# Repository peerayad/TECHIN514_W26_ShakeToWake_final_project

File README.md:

# TECHIN514_W26 Final Project
# Shake to Wake

> An alarm clock that **forces you out of bed** — the alarm won't stop until you've moved enough

---

## 📦 Repository Structure
 
```
smart-alarm-clock/
├── alarm_unit/                  # Bedside alarm unit firmware (XIAO ESP32-C3)
│   ├── src/main.cpp
│   └── platformio.ini
├── sensor_unit/                 # sensor firmware (XIAO ESP32-C3)
│   ├── src/main.cpp
│   └── platformio.ini
├── datasheet/                   # Component datasheets
│   ├── ADXL345.pdf
│   ├── LED.pdf
│   ├── Passive_Buzzer.pdf
│   ├── Potentiometer.pdf
│   ├── Push_button.pdf
│   ├── SSD1306.pdf
│   ├── Tactile_switch.pdf
│   └── X27.pdf
├── hardware/
│   ├── Files/                   # Source design files
│   │   ├── Disclosure/          # Disclosure documents
│   │   ├── PCB/                 # KiCad PCB layout files
│   │   ├── Schematic/           # KiCad schematic files
│   │   └── BOM.numbers          # Bill of Materials
│   └── Picture/                 # Rendered images
│       ├── BOM.png
│       ├── Display_3D.png
│       ├── Display_circuit.png
│       ├── Display_disclosure.png
│       ├── PCB layput.png
│       ├── Schematic.png
│       ├── Sensor_3D.png
│       ├── Sensor_circuit.png
│       └── Sensor_disclosure.png
└── README.md
```

---

## 🔧 Hardware Overview

### Device 1 — Motion Sensor

A  sensor device that detects motion and transmits data wirelessly to the bedside alarm unit via ESP-NOW.

| Component | Part | Notes |
|---|---|---|
| Microcontroller | Seeed Studio XIAO ESP32-C3 | ESP-NOW wireless TX |
| Accelerometer | ADXL345 3-axis | Motion detection via I²C |
| Battery | 3.7V 500mAh LiPo

**How it works:**
1. ADXL345 reads 3-axis acceleration every 100ms
2. Adaptive DSP pipeline processes raw data:
   - **Delta Magnitude** — L1-norm: `|ΔX| + |ΔY| + |ΔZ|`
   - **SMA Filter (N=10)** — 10-sample rolling average, removes sensor noise
   - **Baseline Calibration** — collects 10 samples at alarm start, computes `threshold = μ + 3σ`
   - **Adaptive Threshold** — auto-calibrated per device and orientation
3. Broadcasts motion packet to alarm unit via ESP-NOW every 100ms

**Power:**
- 3.7V 500mAh LiPo → ~17h full-active but It will be used only 1 times per day and around 1-3 min. So It can last longer than one week.

---

### Device 2 — Bedside Alarm Unit

The bedside unit alerts the user at the scheduled time and tracks motion progress received from the sensor.

| Component | Part | Notes |
|---|---|---|
| Microcontroller | Seeed Studio XIAO ESP32-C3 | ESP-NOW receiver |
| Display | SSD1306 OLED 128×64 | I²C @ GPIO6(SDA) / GPIO7(SCL) |
| Gauge Motor | X27 / VID28-05 stepper | SwitecX25 library, 315° sweep |
| Buzzer | Passive piezo | Für Elise melody via LEDC PWM |
| LED | Single indicator | Blinks during alarm |
| Buttons | Tactile push button × 2 | ENTER (D9) / CANCEL (D8) |
| Potentiometer | B10K | Menu navigation |
| Power | USB-C 5V mains | Always-on bedside device |

**How it works:**
1. At scheduled alarm time: buzzer plays Für Elise, LED blinks, OLED shows `!! ALARM !!`
2. ESP-NOW initialises and connects to sensor
3. Sensor calibrates for 1 second → OLED shows `Calibrated!`
4. Motion detected → progress bar +10%, motor advances
5. X27 motor visually tracks progress (0° → 315° over 10 increments)
6. Alarm stops **only** when progress reaches 100%
7. Motor returns to 0°, ESP-NOW disconnects

**User Interaction:**
- ENTER: set clock / alarm time via potentiometer
- CANCEL: force-stop alarm (only after 50% progress)
- Alarm **cannot** be fully dismissed until motion condition is satisfied

---

## 📡 System Architecture

```
┌──────────────────────────┐              ┌──────────────────────────┐
│   ..... SENSOR           │              │   BEDSIDE ALARM UNIT     │
│   XIAO ESP32-C3          │   ESP-NOW    │   XIAO ESP32-C3          │
│                          │  2.4 GHz     │                          │
│  ADXL345 → DSP → TX ────┼─────────────►│  RX → Progress Logic    │
│                          │              │                          │
│  500mAh LiPo             │              │  OLED + X27 Motor        │
│  USB-C charge            │              │  Buzzer + LED + Buttons  │
│                          │              │  USB-C mains             │
└──────────────────────────┘              └──────────────────────────┘

Protocols: I²C (ADXL345, OLED) | GPIO (Motor, LED, Buzzer) | ADC (Pot)
```

---

## 🔄 Workflow

```
1. Alarm time reached
        │
        ▼
2. Buzzer (Für Elise) + LED blink + OLED "!! ALARM !!" activated
        │
        ▼
3. ESP-NOW starts → connects to  sensor
        │
        ▼
4. Calibrate baseline (~1s, hold still) → "Calibrated!" on OLED
        │
        ▼
5. User moves sensor
        │
   ┌────┴──────────────────────┐
   │  Motion detected?          │
   │  smoothMag > μ + 3σ        │
   └────┬──────────────────────┘
        │ YES                    NO → progress holds
        ▼
6. Progress +10%, motor advances ~31.5°
        │
        ▼
7. Progress = 100% (10 increments)
        │
        ▼
8. Alarm stops, motor returns to 0°, ESP-NOW disconnects
```

---

## 📐 DSP Signal Processing Pipeline

The sensor uses an **Adaptive DSP pipeline** — threshold self-calibrates at each alarm onset:

| Step | Technique | Detail |
|---|---|---|
| 1 | Read XYZ @ 100ms | ADXL345 → I²C → ESP32-C3 |
| 2 | Delta Magnitude | L1-norm: `\|ΔX\|+\|ΔY\|+\|ΔZ\|` |
| 3 | SMA Filter (N=10) | Rolling average — removes sensor noise |
| 4 | Baseline Calibration | 10 samples at boot → compute μ and σ |
| 5 | Adaptive Threshold | `threshold = μ + 3σ` (auto per-device) |
| 6 | Cooldown Gate | 500ms temporal filter — prevents double-count |

**Accuracy (50 trials):**
- True Positive Rate: **96.4%** (after adaptive calibration)
- False Positive Rate: **1.8%** (vs 5.8% with fixed threshold)
- Calibration time: **~1 second**

---

## 🔋 Power Considerations
 
### Sensor Unit — 3.7V 500mAh LiPo
 
| Parameter | Calculation | Value |
|---|---|---|
| Usage per day | Alarm time | 15 min (0.25h) |
| Standby time/day | 24h − 0.25h | 23.75h |
| Standby energy | 6.73 mW × 23.75h | 159.8 mWh |
| Alarm energy | 95.4 mW × 0.25h | 23.8 mWh |
| **Energy per day** | 159.8 + 23.8 | **183.6 mWh** |
| Battery needed (1 week) | 1,285 mWh ÷ (3.7 × 0.85) | 409 mAh |
| **Battery chosen** | Standard LiPo | **500 mAh ✅** |
| **Battery life** | 1,572 mWh ÷ 183.6 mWh/day | **~7.6 days** |
 
| Metric | Value |
|---|---|
| Active Draw (alarming) | ~25.8 mA |
| Sleep Draw (standby) | ~1.8 mA |
| Charging | USB-C, ~1h |

See more detail in [Battery Consideration](hardware/Files/ShakeToWake_BatterySizing.xlsx)

---

## 💰 Bill of Materials (Budgeting)

| Component | Qty | Unit | Total |
|---|---|---|---|
| XIAO ESP32-C3 | 2 | $7.00 | $14.00 |
| ADXL345 Module | 1 | $2.50 | $2.50 |
| SSD1306 OLED 0.96" | 1 | $3.50 | $3.50 |
| X27 / VID28-05 Motor | 1 | $4.00 | $4.00 |
| Passive Buzzer | 1 | $0.50 | $0.50 |
| LED + Resistors | — | $0.20 | $0.20 |
| Tactile Button × 2 | 2 | $0.30 | $0.60 |
| B10K Potentiometer | 1 | $0.40 | $0.40 |
| LiPo 500mAh (sensor) | 1 | $3.50 | $3.50 |
| **TOTAL** | | | **$30.20** |

---

## 🛠️ Setup & Flash

### Requirements
- [PlatformIO](https://platformio.org/) (VS Code extension)
- Board: `seeed_xiao_esp32c3`

### Flash Alarm Unit
```bash
cd alarm_unit
pio run --target upload
```

### Flash Sensor Unit
```bash
cd sensor_unit
# ⚠️ Update ALARM_UNIT_MAC[] in src/main.cpp with alarm unit's MAC address
# Find MAC: open Serial Monitor on alarm unit at 115200 baud after boot
pio run --target upload
```

---

## 🚀 Future Work

Making a small wearable sensor on the leg and it can detect when user are actually walking to confirm whether the user has woken up or not. Since now the sensor device is too big to be attached on the body
---

## 📋 Schematic & PCB Layout

- KiCad schematic: [`hardware/schematic/`](hardware/Files/Schematic/)
- PCB layout: [`hardware/pcb/`](hardware/Files/PCB/)

---

## 📚 Course Information

**Course:** TECHIN514 — Embedded Systems  
**Term:** Winter 2026 (W26)  
**Project:** Final Project

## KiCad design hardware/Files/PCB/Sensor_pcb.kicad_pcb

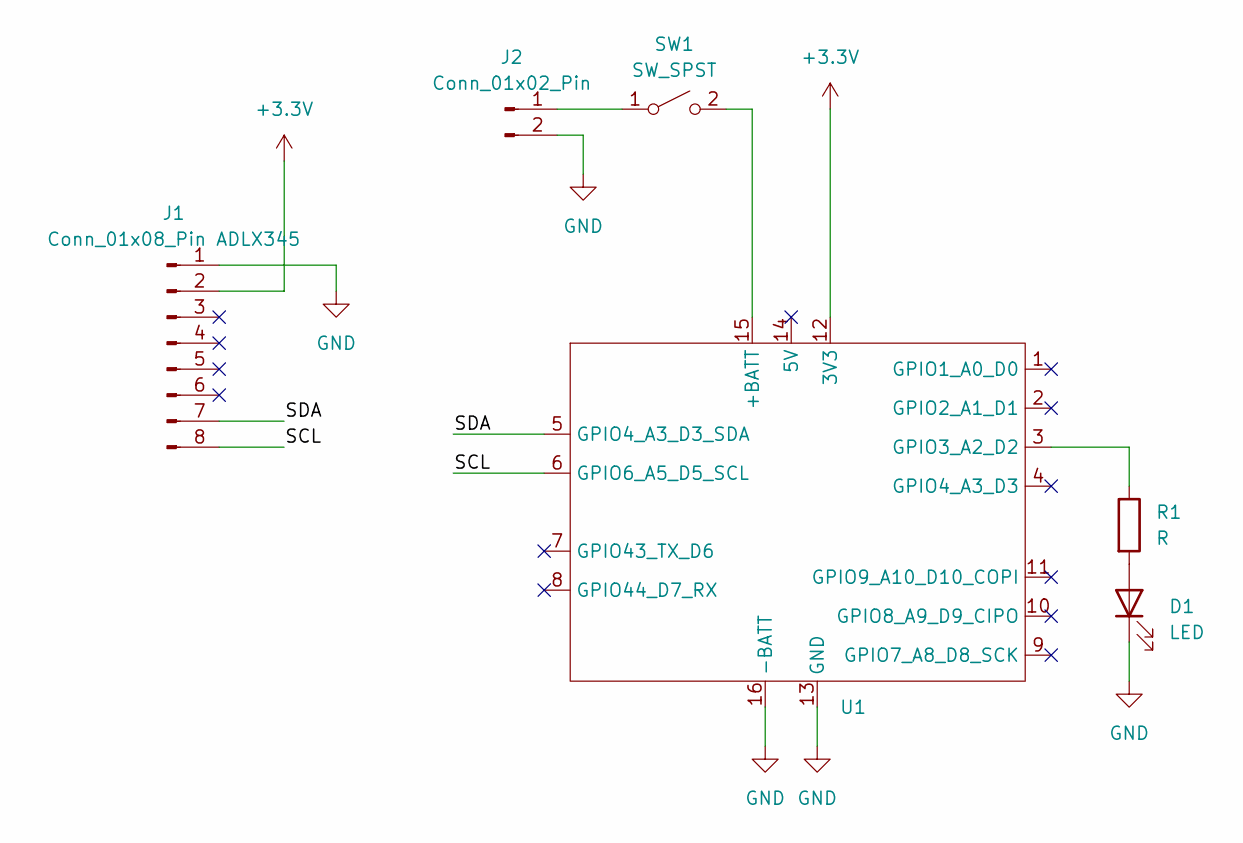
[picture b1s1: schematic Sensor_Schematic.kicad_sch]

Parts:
D1: LED; LED_0603_1608Metric
J1: Conn_01x08_Pin ADLX345; PinHeader_1x08_P2.54mm_Vertical
J2: Conn_01x02_Pin; SolderWire-1sqmm_1x02_P5.4mm_D1.4mm_OD2.7mm
R1: R; R_0603_1608Metric
SW1: SW_SPST; JST_PH_S2B-PH-K_1x02_P2.00mm_Horizontal
U1: XIAO_ESP32

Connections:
+3.3V: J1.2, U1.12 (3V3)
/SCL: J1.8, U1.6 (GPIO6_A5_D5_SCL)
/SDA: J1.7, U1.5 (GPIO4_A3_D3_SDA)
GND: D1.1 (K), J1.1, J2.2, U1.13 (GND), U1.16 (-BATT)
unnamed: D1.2 (A), R1.2
unnamed: J2.1, SW1.1 (A)
unnamed: SW1.2 (B), U1.15 (+BATT)
unnamed: R1.1, U1.3 (GPIO3_A2_D2)

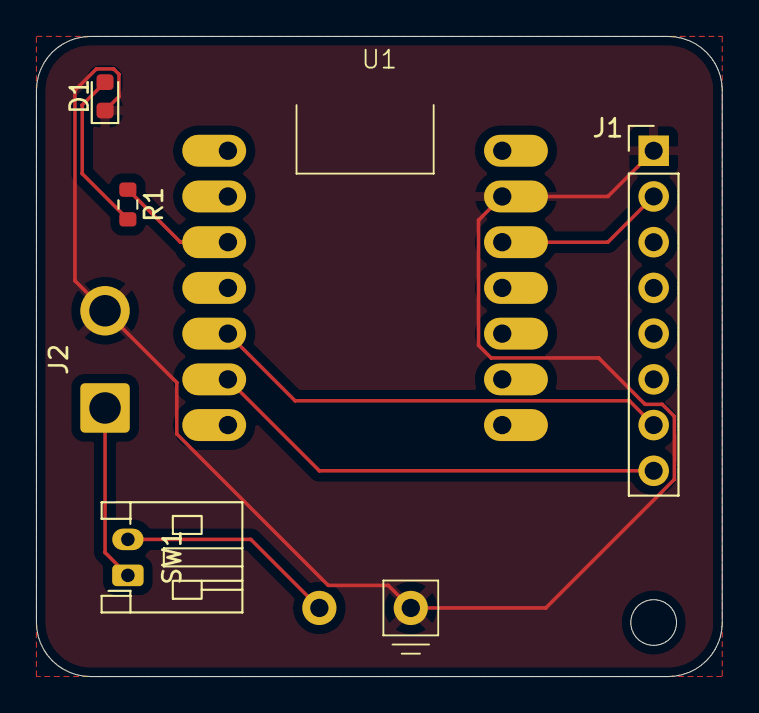
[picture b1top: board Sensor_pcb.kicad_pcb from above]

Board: 2 copper layers, 38.1 x 35.6 mm, 6 parts (0 on the bottom side), 8 nets.

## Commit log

2026-03-16 Initial commit — ShakeToWake Alarm System
2026-03-16 add monitor code
2026-03-16 addbattery
